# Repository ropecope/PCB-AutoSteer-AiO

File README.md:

# PCB-AutoSteer with Arduino Nano All in One
AutoSteer For AgOpenGPS <br> 
AGOpenGPS <br>
Home: https://agopengps.jimdosite.com/ <br>
GitHub: https://github.com/farmerbriantee/AgOpenGPS <br>

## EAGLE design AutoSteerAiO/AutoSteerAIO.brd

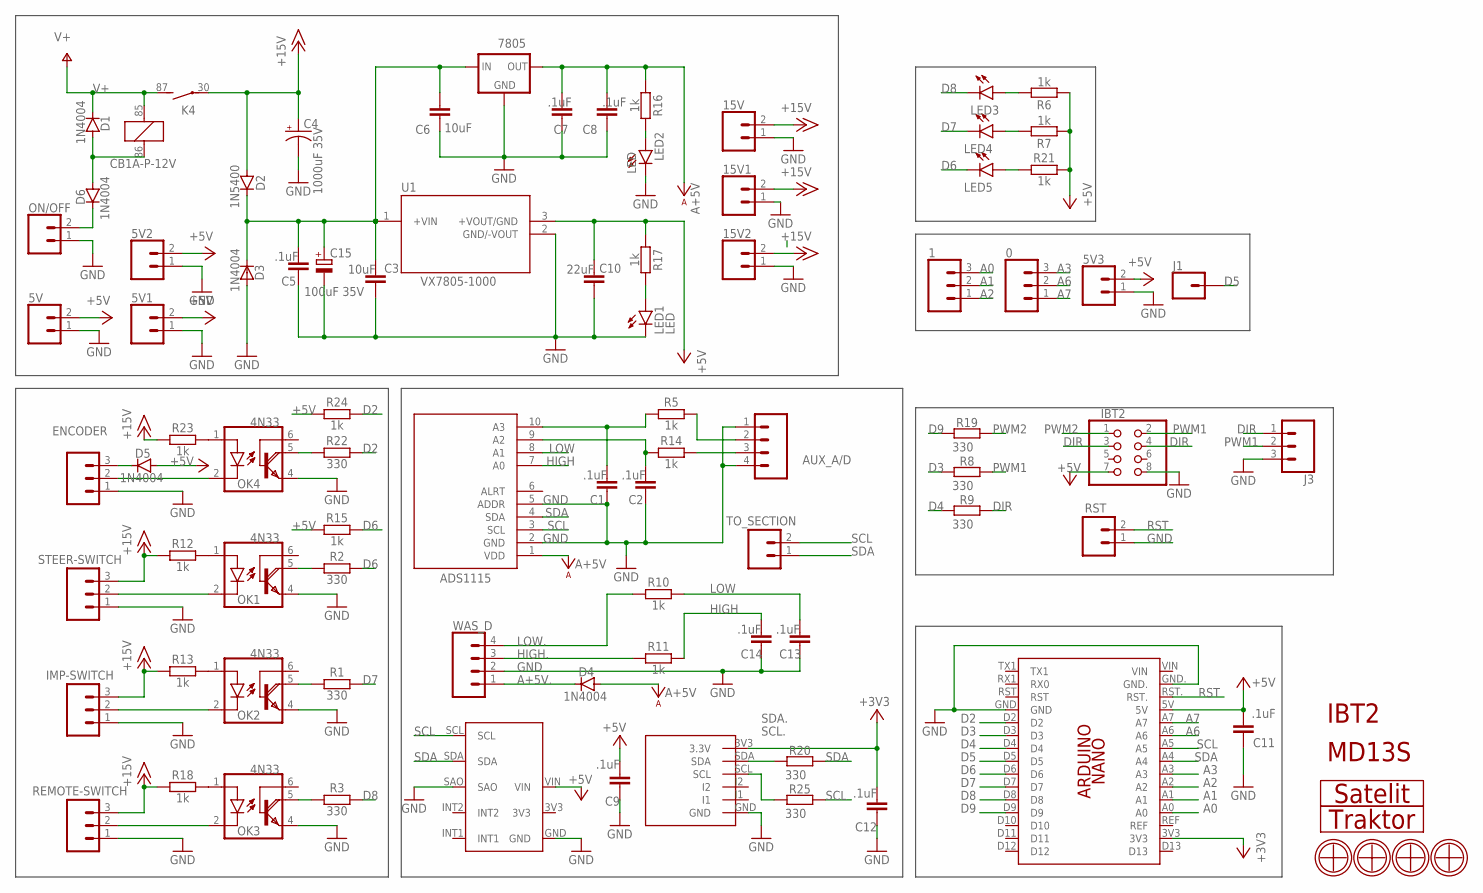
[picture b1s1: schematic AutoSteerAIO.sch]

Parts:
0, 1: CONNECTOR 1x2 PINS; 1X03
5V, 5V1, 5V2, 5V3, 15V, 15V1, 15V2: CONNECTOR 1x2 PINS; 1X02
7805: 78XXS
ADS1115: ADS1115; ADC-4CH-ADS1115
AUX_A/D: CONNECTOR 1x4 PINS; 1X04
C1, C2, C5, C7, C8, C9, C11, C12, C13, C14: .1uF; C050-024X044
C3, C6: 10uF; C050-024X044
C4: 1000uF 35V; CPOL-RADIAL-5MM-10MM
C10: 22uF; C050-024X044
C15: 100uF 35V; E2,5-6
D1, D3, D4, D5, D6: 1N4004; DO41-10
D2: 1N5400; DO201-15
ENCODER: CONNECTOR 1x3 PINS; 1X03
IBT2: PINHD-2X4; 2X04
IMP-SWITCH: CONNECTOR 1x3 PINS; 1X03
J1: CONN_01; 1X01
J3: CONN_03; 1X03
K4: CB1A-P-12V; CB1
LED1, LED2, LED3, LED4, LED5: LED; LED3MM
MMA8542: MMA8542; MMA8452
OK1, OK2, OK3, OK4: 4N33; DIL06
ON/OFF: CONNECTOR 1x2 PINS; 1X02
PCB1: ARDUINO NANO v3; ARDUINO-NANO
R1, R2, R3, R8, R9, R19, R20, R22, R25: 330; 0207/7
R5, R6, R7, R10, R11, R12, R13, R14, R15, R16, R17, R18, R21, R23, R24: 1k; 0207/7
REMOTE-SWITCH: CONNECTOR 1x3 PINS; 1X03
RST: CONNECTOR 1x2 PINS; 1X02
STEER-SWITCH: CONNECTOR 1x3 PINS; 1X03
TO_SECTION: CONNECTOR 1x2 PINS; 1X02
U1: VX7805-1000; VX78012-1000_VX7805-1000
U$1: MD13S
U$2: IBT2
U$5: TRAKTOR-MALI
U$6, U$7, U$9, U$10: 4.2MM-6MM
U$8: SATELIT-MALI
U$13: MMA8542Q
WAS_D: CONNECTOR 1x4 PINS; 1X04

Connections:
+3V3: C12.2, PCB1.3V3, U$13.3V3 (3.3V)
+5V: 5V.2, 5V1.2, 5V2.2, 5V3.2, C9.2, C10.2, C11.2, D5.A, IBT2.7, MMA8542.VIN, PCB1.5V, R6.1, R7.1, R15.1, R17.1, R21.2, R24.1, U1.3 (+VOUT/GND)
+15V: 15V.2, 15V1.2, 15V2.2, C4.+, D2.A, IMP-SWITCH.3, K4.30, R12.1, R13.1, R18.1, R23.1, REMOTE-SWITCH.3, STEER-SWITCH.3
A0: 1.3, PCB1.A0
A1: 1.2, PCB1.A1
A2: 1.1, PCB1.A2
A3: 0.3, PCB1.A3
A6: 0.2, PCB1.A6
A7: 0.1, PCB1.A7
A+5V: 7805.OUT, ADS1115.1 (VDD), C7.2, C8.2, D4.A, R16.1
A+5V.: D4.C, WAS_D.1
D2: PCB1.D2, R22.2, R24.2
D3: PCB1.D3, R8.2
D4: PCB1.D4, R9.2
D5: J1.1, PCB1.D5
D6: LED5.K (C), PCB1.D6, R2.2, R15.2
D7: LED4.K (C), PCB1.D7, R1.2
D8: LED3.K (C), PCB1.D8, R3.2
D9: PCB1.D9, R19.2
DIR: IBT2.3, IBT2.4, J3.1, R9.1
GND: 5V.1, 5V1.1, 5V2.1, 5V3.1, 15V.1, 15V1.1, 15V2.1, 7805.GND, ADS1115.2 (GND), ADS1115.5 (ADDR), AUX_A/D.1, AUX_A/D.4, C1.1, C2.1, C3.1, C4.-, C5.1, C6.1, C7.1, C8.1, C9.1, C10.1, C11.1, C12.1, C13.1, C14.1, C15.-, D3.A, ENCODER.1, IBT2.8, IMP-SWITCH.1, J3.3, LED1.K (C), LED2.K (C), MMA8542.GND, MMA8542.SAO, OK1.4 (E), OK2.4 (E), OK3.4 (E), OK4.4 (E), ON/OFF.1, PCB1.GND, PCB1.GND., REMOTE-SWITCH.1, RST.1, STEER-SWITCH.1, U1.2 (GND/-VOUT), U$13.GND, WAS_D.2
HIGH: ADS1115.7 (A0), C14.2, R11.2
HIGH.: R11.1, WAS_D.3
LOW: ADS1115.8 (A1), C13.2, R10.2
LOW.: R10.1, WAS_D.4
unnamed: D5.C, ENCODER.3
unnamed: OK1.5 (COL), R2.1
unnamed: OK1.2 (C), STEER-SWITCH.2
unnamed: IMP-SWITCH.2, OK2.2 (C)
unnamed: D1.A, D6.A, K4.86 (1)
unnamed: OK2.5 (COL), R1.1
unnamed: ADS1115.10 (A3), C1.2, R5.1
unnamed: ADS1115.9 (A2), C2.2, R14.1
unnamed: ENCODER.2, OK4.2 (C)
unnamed: AUX_A/D.2, R5.2
unnamed: AUX_A/D.3, R14.2
unnamed: OK3.2 (C), REMOTE-SWITCH.2
unnamed: LED2.A, R16.2
unnamed: LED1.A, R17.2
unnamed: OK3.5 (COL), R3.1
unnamed: OK2.1 (A), R13.2
unnamed: OK3.1 (A), R18.2
unnamed: OK1.1 (A), R12.2
unnamed: LED3.A, R6.2
unnamed: LED5.A, R21.1
unnamed: 7805.IN, C3.2, C5.2, C6.2, C15.+, D2.C, D3.C, U1.1 (+VIN)
unnamed: D6.C, ON/OFF.2
unnamed: OK4.5 (COL), R22.1
unnamed: OK4.1 (A), R23.2
unnamed: LED4.A, R7.2
PWM1: IBT2.2, J3.2, R8.1
PWM2: IBT2.1, R19.1
RST: PCB1.RST., RST.2
SCL: ADS1115.3 (SCL), MMA8542.SCL, PCB1.A5, R25.1, TO_SECTION.2
SCL.: R25.2, U$13.SCL
SDA: ADS1115.4 (SDA), MMA8542.SDA, PCB1.A4, R20.1, TO_SECTION.1
SDA.: R20.2, U$13.SDA
V+: D1.C, K4.85 (2), K4.87 (S)

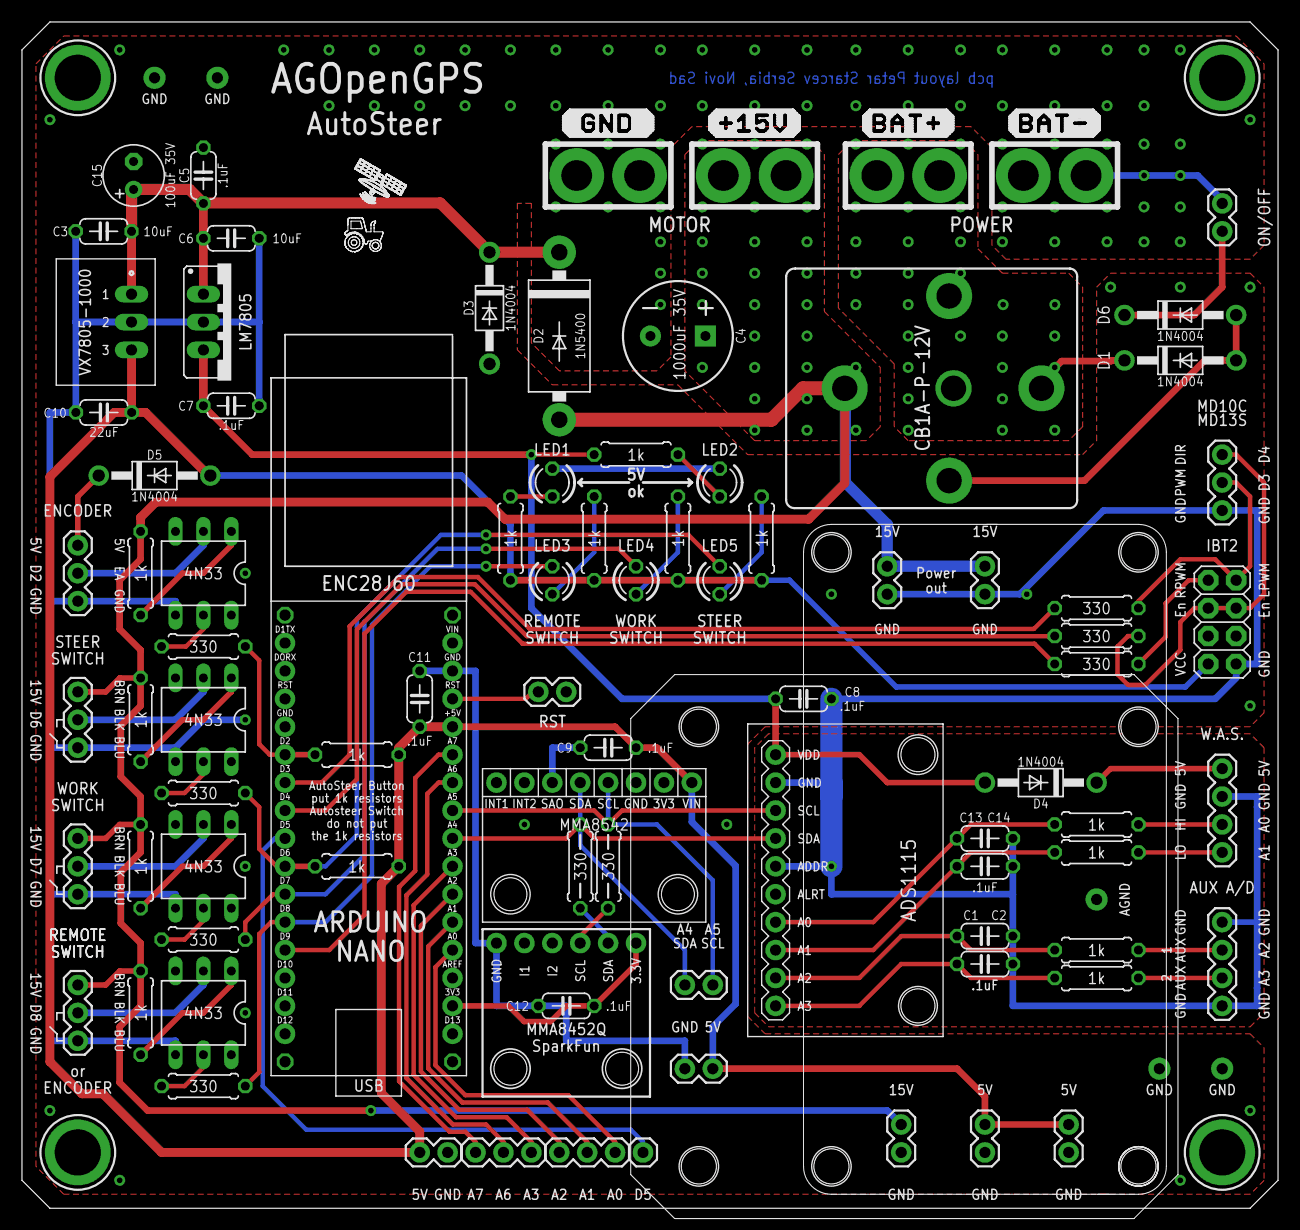
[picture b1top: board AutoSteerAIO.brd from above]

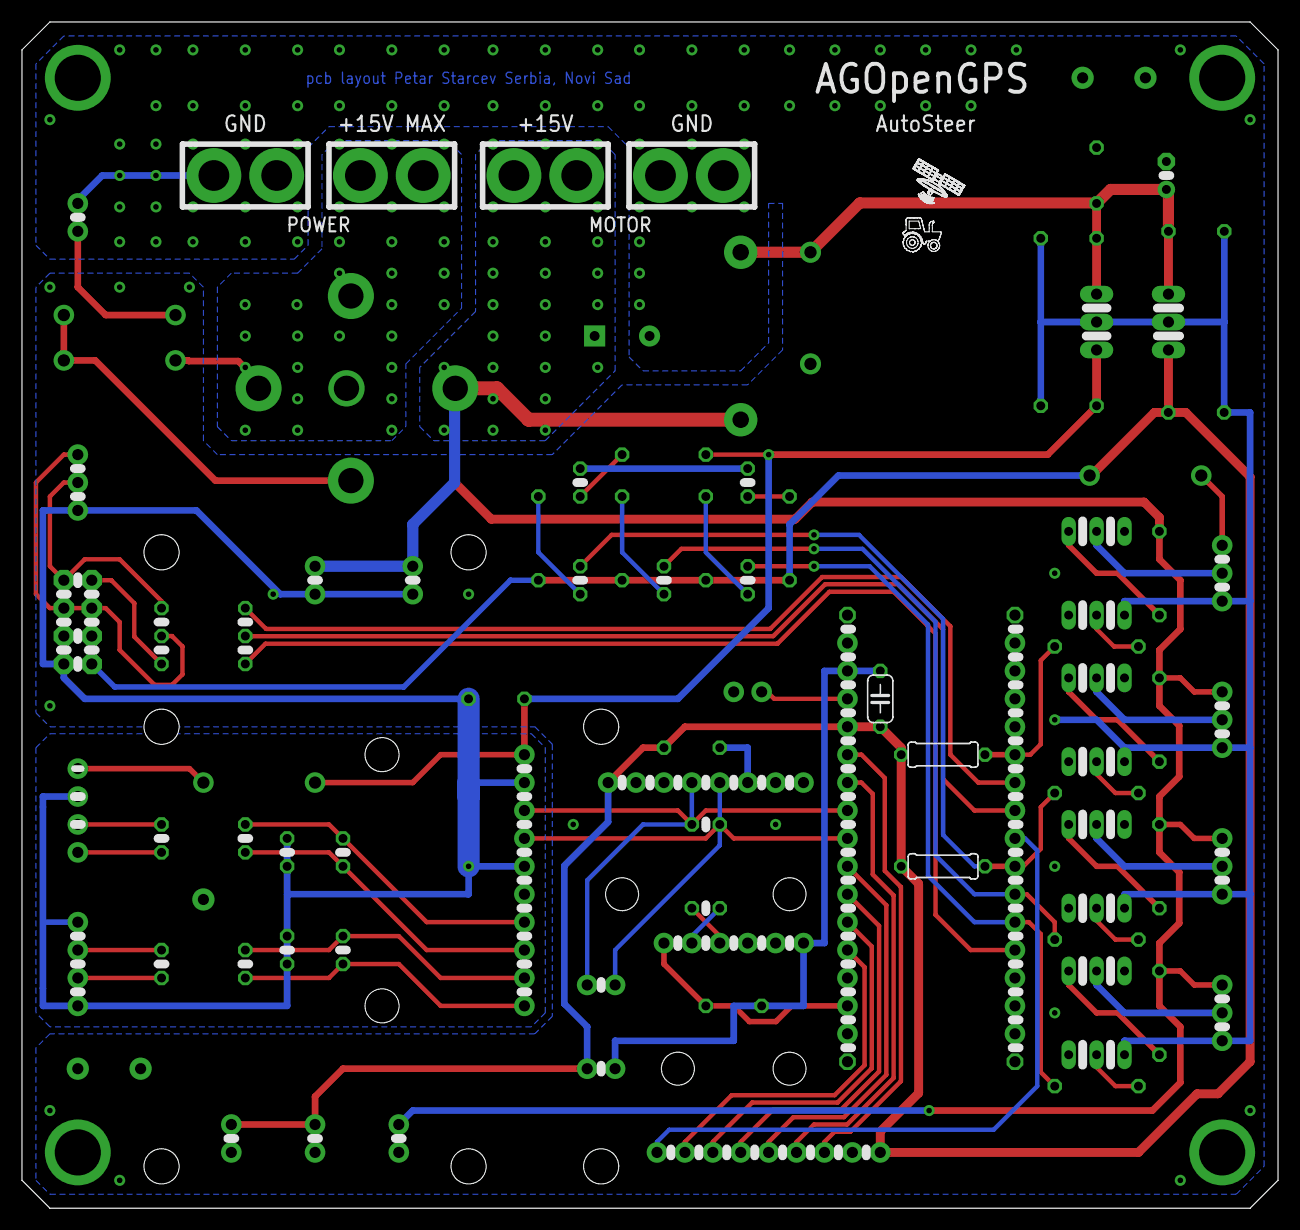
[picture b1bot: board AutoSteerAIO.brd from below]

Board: 2 copper layers, 114.3 x 108.0 mm, 92 parts (2 on the bottom side), 58 nets.

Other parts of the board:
U$11: SATELIT-MALI
U$12: TRAKTOR-MALI

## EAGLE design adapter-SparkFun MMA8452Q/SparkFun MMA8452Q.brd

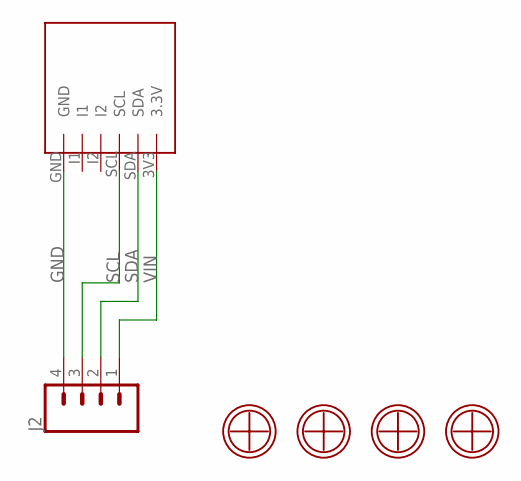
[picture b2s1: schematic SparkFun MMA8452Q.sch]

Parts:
J2: CONN_04; 1X04
U$1, U$2, U$3, U$4: 3.2MM-5MM
U$5: MMA8542Q

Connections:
GND: J2.4, U$5.GND
SCL: J2.3, U$5.SCL
SDA: J2.2, U$5.SDA
VIN: J2.1, U$5.3V3 (3.3V)

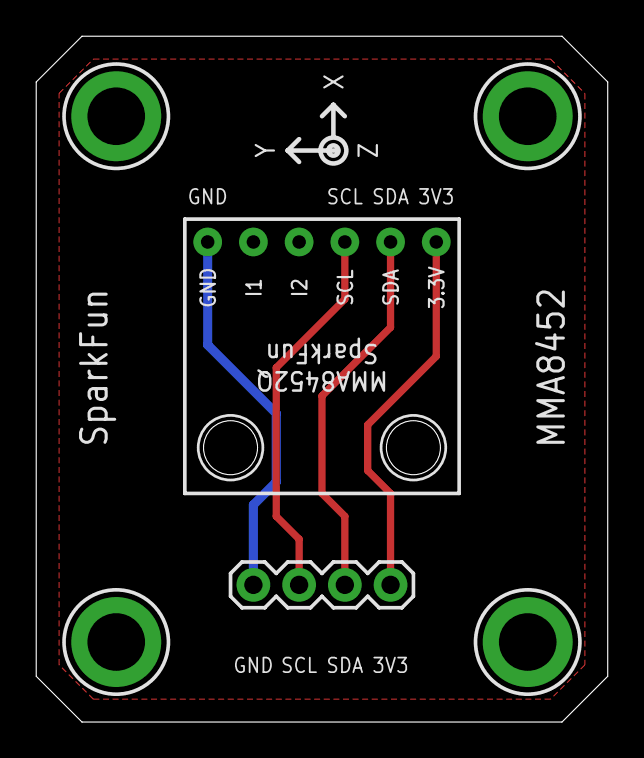
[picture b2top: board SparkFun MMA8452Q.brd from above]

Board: 2 copper layers, 31.8 x 38.1 mm, 6 parts (0 on the bottom side), 4 nets.

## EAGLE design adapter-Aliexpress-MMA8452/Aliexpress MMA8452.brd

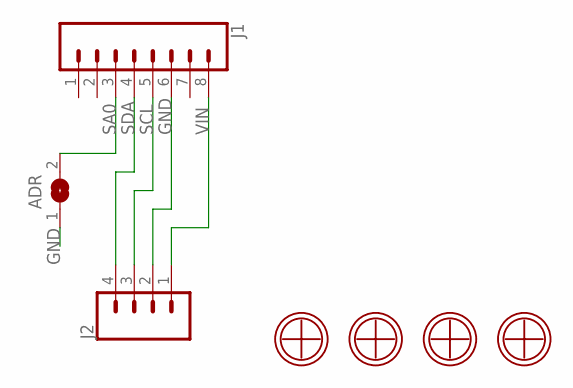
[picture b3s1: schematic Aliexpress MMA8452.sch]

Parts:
ADR: SOLDERJUMPERREFLOW; SOLDERJUMPER_REFLOW
J1: CONN_08"; 1X08
J2: CONN_04; 1X04
U$1, U$2, U$3, U$4: 3.2MM-5MM

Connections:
GND: ADR.1, J1.6, J2.2
SA0: ADR.2, J1.3
SCL: J1.5, J2.3
SDA: J1.4, J2.4
VIN: J1.8, J2.1

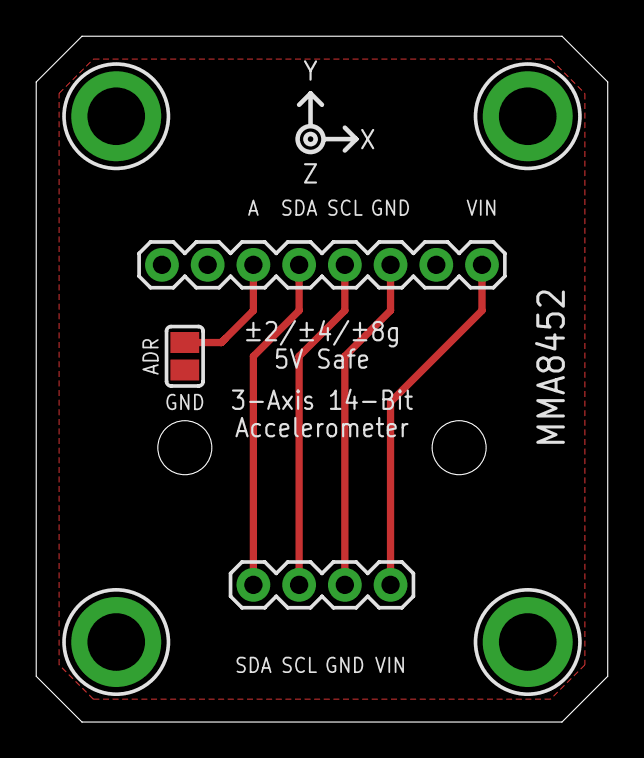
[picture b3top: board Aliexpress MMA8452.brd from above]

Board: 2 copper layers, 31.8 x 38.1 mm, 7 parts (0 on the bottom side), 5 nets.

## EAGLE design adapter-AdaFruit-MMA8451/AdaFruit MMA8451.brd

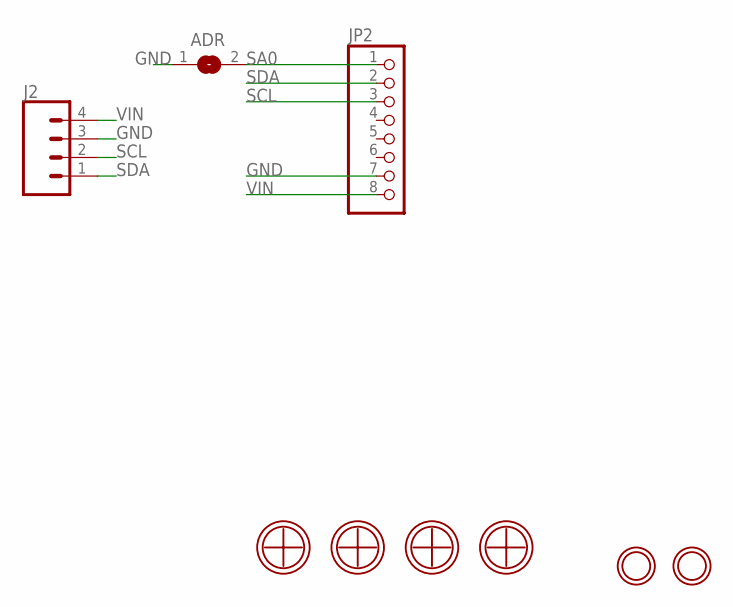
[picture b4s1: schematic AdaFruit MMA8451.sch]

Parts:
ADR: SOLDERJUMPERREFLOW; SOLDERJUMPER_REFLOW
J2: CONN_04; 1X04
JP2: HEADER-1X870MIL; 1X08_ROUND_70
U$1, U$2: MOUNTINGHOLE2.5; MOUNTINGHOLE_2.5_PLATED
U$3, U$4, U$5, U$6: 3.2MM-5MM

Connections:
GND: ADR.1, J2.3, JP2.7
SA0: ADR.2, JP2.1
SCL: J2.2, JP2.3
SDA: J2.1, JP2.2
VIN: J2.4, JP2.8

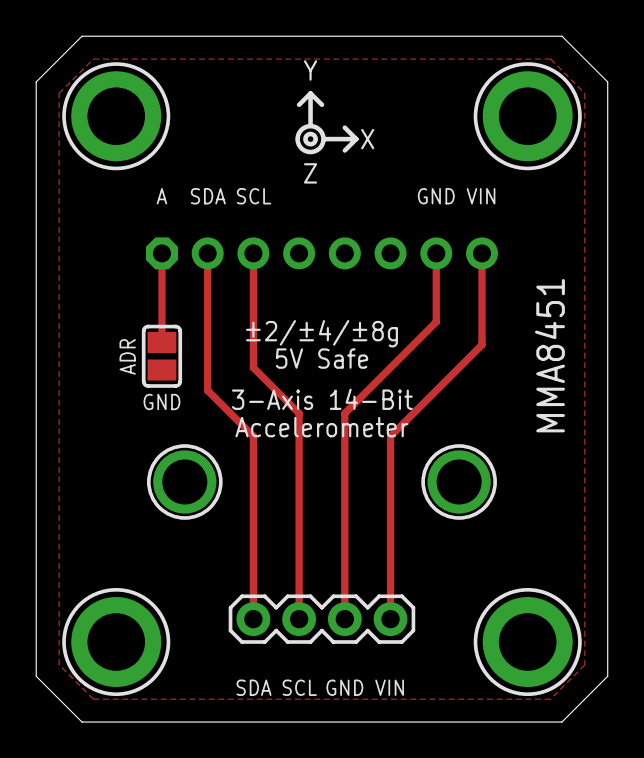
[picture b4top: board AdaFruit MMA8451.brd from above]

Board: 2 copper layers, 31.8 x 38.1 mm, 9 parts (0 on the bottom side), 5 nets.

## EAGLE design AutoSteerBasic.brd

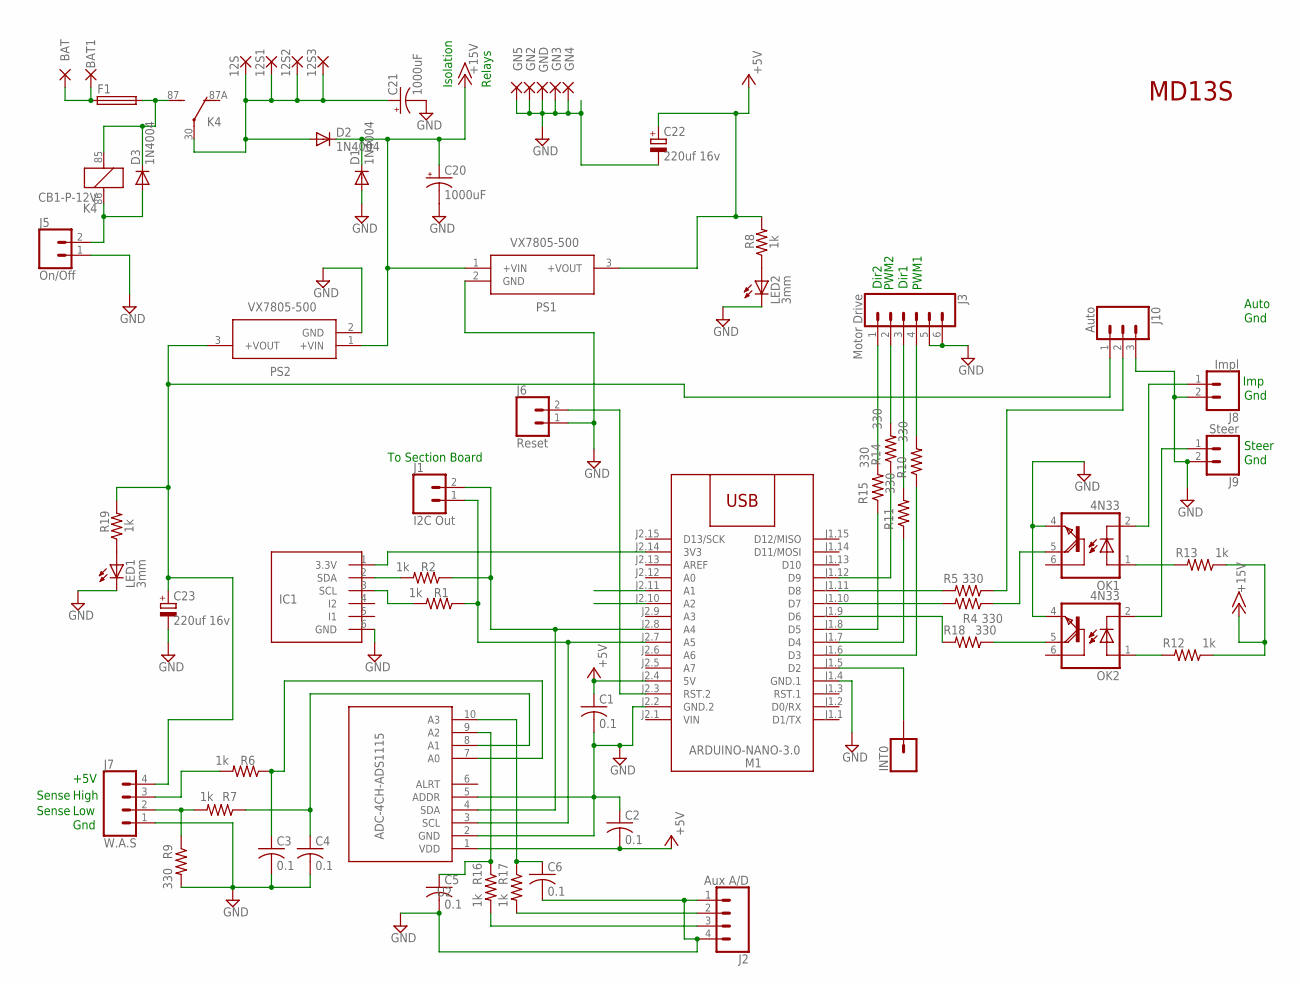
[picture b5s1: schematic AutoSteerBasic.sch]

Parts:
12S, 12S1, 12S2, 12S3: WIREPAD3,81/1,1; 3,81/1,1
BAT, BAT1: WIREPAD3,81/1,1; 3,81/1,1
C1, C2, C3, C4, C5, C6: 0.1; C025-025X050
C20, C21: 1000uF; CPOL-RADIAL-5MM-10MM
C22, C23: 220uf 16v; E3,5-8
D1, D2, D3: 1N4004; DO41-10
F1: SHK20L
GN2, GN3, GN4, GN5: WIREPAD3,81/1,1; 3,81/1,1
GND: WIREPAD3,81/1,1; 3,81/1,1
IC1: MMA8452Q; BREAKOUT_6PIN
INT0: CONN_01PTH_LONGPAD; 1X01_LONGPAD
J1: I2C Out; 1X02_LONGPADS
J2: Aux A/D; 1X04_LONGPADS
J3: Motor Drive; 1X06_LONGPADS
J5: On/Off; 1X02_LONGPADS
J6: Reset; 1X02_LONGPADS
J7: W.A.S; 1X04_LONGPADS
J8: Impl; 1X02_LONGPADS
J9: Steer; 1X02_LONGPADS
J10: Auto; 1X03_LONGPADS
K4: CB1-P-12V; CB1
LED1, LED2: 3mm; LED3MM
M1: ARDUINO-NANO-3.0
OK1, OK2: 4N33; DIL06
PS1, PS2: VX7805-500; VX7805500
R1, R2, R6, R7, R8, R12, R13, R16, R17, R19: 1k; 0207/7
R4, R5, R9, R10, R11, R14, R15, R18: 330; 0207/7
U2: ADC-4CH-ADS1115
U$2: MD13S

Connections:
+5V: C1.1, C2.2, C22.+, M1.J2.4 (5V), PS1.3 (+VOUT), R8.2, U2.1 (VDD)
+15V: C20.+, D1.C, D2.C, PS1.1 (+VIN), PS2.1 (+VIN), R12.1, R13.1
BATT: BAT.1, BAT1.1, F1.1A
FUSED: D3.C, F1.2A, K4.85 (2), K4.87 (S)
GND: C1.2, C2.1, C3.2, C4.2, C5.2, C6.2, C20.-, C21.-, C22.-, C23.-, D1.A, GN2.1, GN3.1, GN4.1, GN5.1, GND.1, IC1.6 (GND), J2.1, J2.4, J3.5, J3.6, J5.1, J6.1, J7.1, J8.2, J9.2, J10.3, LED1.K (C), LED2.K (C), M1.J1.4 (GND.1), M1.J2.2 (GND.2), OK1.4 (E), OK2.4 (E), PS1.2 (GND), PS2.2 (GND), R9.2, U2.2 (GND), U2.5 (ADDR)
unnamed: IC1.1 (3.3V), M1.J2.14 (3V3)
unnamed: J7.2, R7.2, R9.1
unnamed: M1.J1.6 (D3), R10.1
unnamed: M1.J1.7 (D4), R11.1
unnamed: INT0.1, M1.J1.5 (D2)
unnamed: J6.2, M1.J2.3 (RST.2)
unnamed: J7.3, R6.2
unnamed: M1.J1.8 (D5), R15.1
unnamed: M1.J1.12 (D9), R14.1
unnamed: IC1.2 (SDA), R2.2
unnamed: IC1.3 (SCL), R1.2
unnamed: J1.2, M1.J2.8 (A4), R2.1, U2.4 (SDA)
unnamed: LED2.A, R8.1
unnamed: LED1.A, R19.1
unnamed: J3.4, R10.2
unnamed: J1.1, M1.J2.7 (A5), R1.1, U2.3 (SCL)
unnamed: J3.3, R11.2
unnamed: C3.1, R6.1, U2.7 (A0)
unnamed: J3.2, R14.2
unnamed: J3.1, R15.2
unnamed: M1.J1.11 (D8), R5.2
unnamed: D3.A, J5.2, K4.86 (1)
unnamed: OK2.1 (A), R12.2
unnamed: M1.J1.10 (D7), R4.2
unnamed: J8.1, OK1.2 (C)
unnamed: M1.J1.9 (D6), R18.2
unnamed: OK1.1 (A), R13.2
unnamed: J9.1, OK2.2 (C)
unnamed: J10.2, R5.1
unnamed: C6.1, R17.1, U2.10 (A3)
unnamed: C5.1, R16.1, U2.9 (A2)
unnamed: OK1.5 (COL), R4.1
unnamed: J2.2, R17.2
unnamed: OK2.5 (COL), R18.1
unnamed: C4.1, R7.1, U2.8 (A1)
unnamed: J2.3, R16.2
SW_RAW: 12S.1, 12S1.1, 12S2.1, 12S3.1, C21.+, D2.A, K4.30
V+WAS: C23.+, J7.4, J10.1, PS2.3 (+VOUT), R19.2
VIN: M1.J2.1 (VIN)

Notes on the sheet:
Gnd
Low
High
+5V
PWM1
PWM2
Dir1
Dir2
Steer
Imp
Sense
Auto
To Section Board
Isolation
Relays

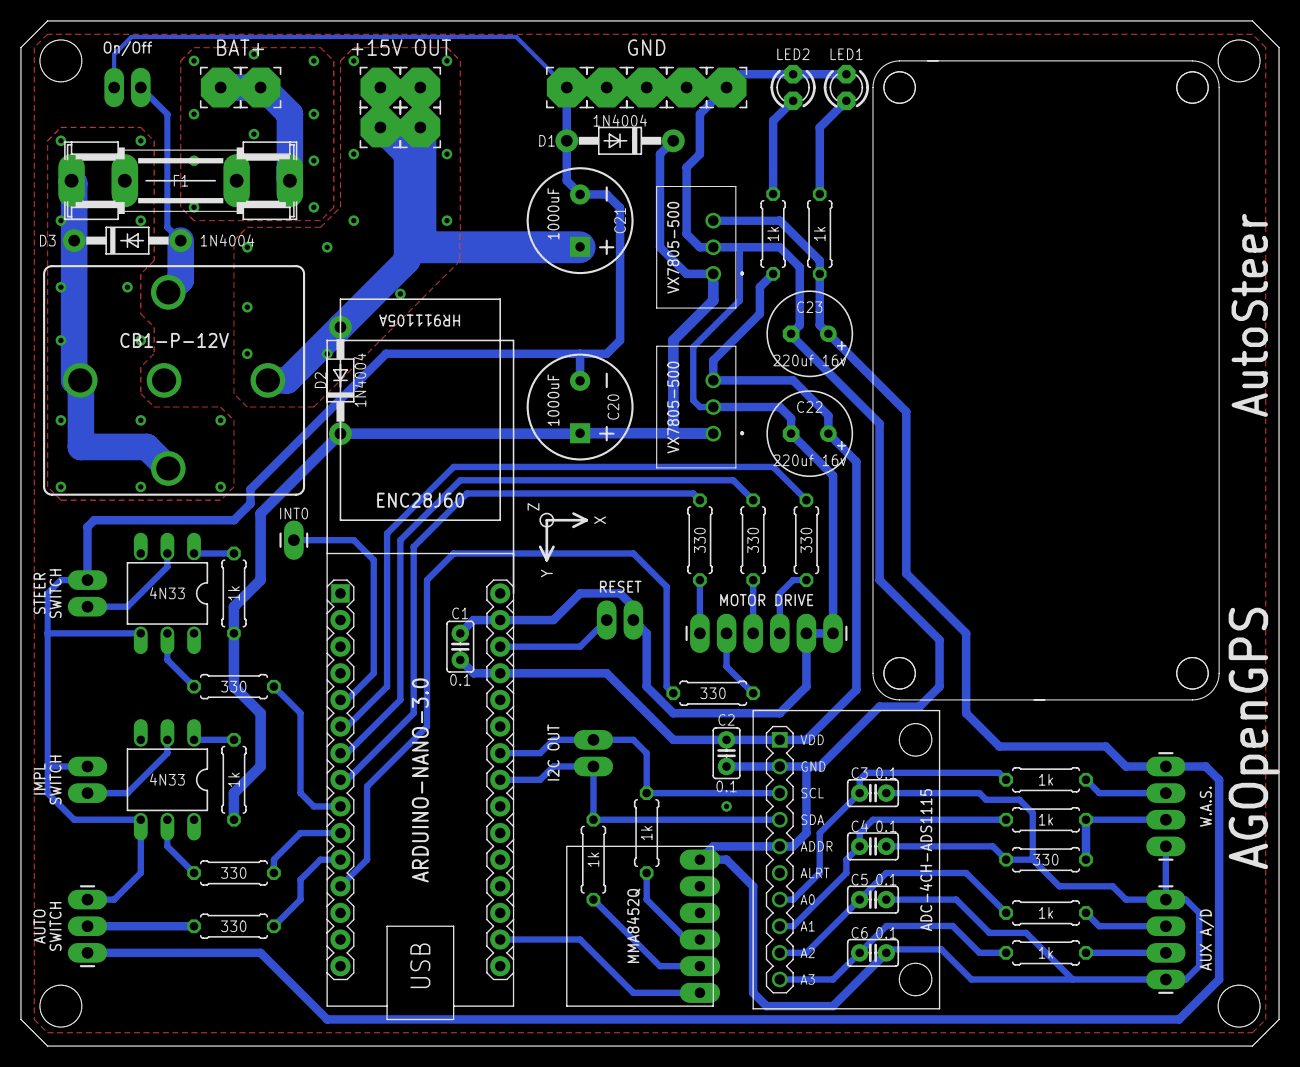
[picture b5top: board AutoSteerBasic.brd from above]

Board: 2 copper layers, 120.0 x 97.8 mm, 64 parts (0 on the bottom side), 43 nets.

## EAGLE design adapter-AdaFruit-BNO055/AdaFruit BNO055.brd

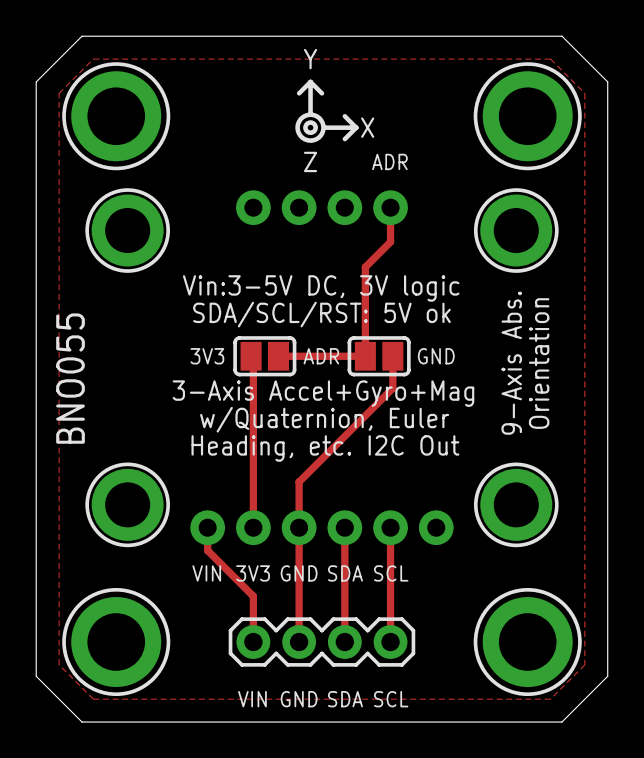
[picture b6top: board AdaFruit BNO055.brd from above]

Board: 2 copper layers, 31.7 x 38.1 mm, 13 parts (0 on the bottom side), 6 nets.

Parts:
ADR, ADR1: SOLDERJUMPER_REFLOW
J2: 1X04
JP3: 1X06_ROUND_76
JP4: 1X04_ROUND_76
U$1, U$3, U$4, U$5: 3.2MM-5MM
U$7, U$8, U$9, U$11: MOUNTINGHOLE2.5_THICK; MOUNTINGHOLE_2.5_PLATED_THICK

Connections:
5.0V: J2.4, JP3.1
GND: ADR1.1, J2.3, JP3.3
unnamed: ADR.2, ADR1.2, JP4.4
unnamed: ADR.1, JP3.2
SCL_5V: J2.1, JP3.5
SDA_5V: J2.2, JP3.4

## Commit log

2019-03-19 Add files via upload
    silkscreen edit
2019-03-20 Add files via upload
    Added MD10C driver
2019-03-20 Add files via upload
    added MD10C holes
2019-03-20 Add files via upload
    edit silkscreen
2019-03-20 Add files via upload
    edit ground plane
2019-03-21 Add files via upload
    Corrected error that was on the A/D converter resistor 330 with sense high moved to sense low
2019-03-21 Add files via upload
    Corrected error that was on the A/D converter resistor 330 with sense high moved to sense low.
2019-03-21 Add files via upload
    add the direction of movement
2019-03-21 Add files via upload
    added the direction of movement
2019-03-21 Add files via upload
    added bottom silkscreen
2019-03-21 Add files via upload
    silkscreen
2019-03-22 Add files via upload
    bottom silkscreen - edit
2019-03-22 Add files via upload
    wrong footprint VX7805-1000 it can fit but will come out with PCB
2019-03-22 Add files via upload
    wrong footprint VX7805-1000 it can fit, but will come out from PCB
2019-03-22 Add files via upload
    previous version, wrong footprint VX7805-1000 it can fit, but will come out from PCB.
    now it's fixed
2019-03-24 Add files via upload
    Removed capacitor after the VX7805 regulator, same as in datasheet https://www.cui.com/product/resource/vx78-500.pdf
    Figure 4
2019-03-25 Add files via upload
    changed the diodes
2019-03-25 Add files via upload
    changed the diodes.
2019-03-26 Add files via upload
    changed footprint for inductor
2019-03-26 Add files via upload
    -
2019-03-28 Add files via upload
    edit bottom slikscreen
2019-03-29 Add files via upload
    Added pin A0 A1 A2 A3
2019-03-29 Add files via upload
    Added pin A0, A1, A2, A3
2019-03-31 Add files via upload
    Adding jumper SAO
2019-04-01 Add files via upload
    Small edit - silkscreen
2019-04-02 Add files via upload
    Small edit
2019-04-03 Add files via upload
    Added a connector for BNO and MMA
    you can use the adapters to place the sensors out of the board
2019-04-06 Add files via upload
    added led autosteer
2019-04-08 Add files via upload
    Adeed 5V connector for IBT2
2019-04-14 Add files via upload
    Added diode D6 to protect from reverse polarity
2019-04-15 Add files via upload
    Edit top silkscreen
2019-04-20 Add files via upload
    One connector for all motor drivers
2019-04-27 Add files via upload
    Added connector for SWEncoder
2019-04-29 Add files via upload
    Added connector for ibt2 driver for connection with Flat ribbon cable
2019-04-29 Add files via upload
    Added Connector for Encoder, 8 pins connector for IBT2 to be able to connect with Flat ribbon cable...
2019-04-30 Add files via upload
    Extended pads on the relay
2019-05-02 Add files via upload
    Added Led diode IMP, WORK and STEER
2019-05-04 Add files via upload
    replaced VX7805-500 with LM7805 - power supply for W.A.S.
2019-05-14 Add files via upload
    I removed the reset connector from PCB since the arduino nano has an ICSP header on which there is a reset pin, and added the capacitor 1000uF for WAS
2019-06-07 Add files via upload
    Add connector for 15v
2019-08-20 MMA8542Q rotated and i2c connector moved
2019-08-24 Added selector for En IBT2, you can also use the new AutosteerPCBv2.ino sketch
2019-08-24 Added one more 15V connector
2019-12-12 Add files via upload
    I removed the capacitors and the inductor has no need for them

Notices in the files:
parts and their libraries:
SparkFun-Connectors: Licensing: Creative Commons ShareAlike 4.0 International - https://creativecommons.org/licenses/by-sa/4.0
Released under the Creative Commons Attribution 4.0 International License: http://creativecommons.org/licenses/by/4.0
